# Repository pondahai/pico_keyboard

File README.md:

# Pico 8x8 矩陣鍵盤韌體

這是一個基於 Raspberry Pi Pico (RP2040) 的 8x8 (64鍵) 自訂機械鍵盤韌體專案。它使用 Arduino-Pico 核心，並透過 74HC595 和 74HC165 晶片來擴展 I/O，僅用 3 個 GPIO 引腳就完成了 64 個按鍵的掃描。此外，還額外擴展了 2 個 LED 指示燈。

韌體最終將 Pico 模擬成一個標準的 USB HID 鍵盤，可以被任何現代作業系統即插即用，同時保留了方便的序列埠除錯功能。

**「這句話就是用這個鍵盤輸入的」** —— 專案成功的最好證明！

## ✨ 主要功能

*   **高效 I/O 擴展**：僅用 3 個 Pico GPIO 引腳驅動 8x8 (64鍵) 矩陣和 2 個 LED。
*   **USB HID 鍵盤**：被電腦識別為標準鍵盤，隨插即用。
*   **複合式 USB 裝置**：同時啟用鍵盤功能和序列埠，方便即時除錯。
*   **雙模式系統**:
    *   **正常打字模式**: 作為一個標準鍵盤工作。
    *   **除錯模式**: 透過序列埠輸出按鍵的物理座標 `(row, col)`，極大地方便了 Keymap 的配置與修改。
*   **韌體層級熱鍵**：使用 `右Shift` + `左Ctrl` 組合鍵在兩種模式間自由切換。
*   **LED 狀態指示**:
    *   LED 1: （目前留空，可自訂，例如用於 CapsLock 指示）。
    *   LED 2: 指示當前是否處於除錯模式（亮起 = 除錯模式）。
*   **全鍵無衝 (NKRO)**：底層支援 6-Key Rollover，可透過修改 HID 報告描述符實現全鍵無衝。
*   **高度客製化**: 使用者可以透過修改 `keymap` 陣列輕鬆定義自己的按鍵佈局。
*   **可靠的掃描邏輯**:
    *   採用「二段式脈衝」確保掃描時序穩定。
    *   第一段脈衝給595輸出 第二段脈衝給165載入 
    *   針對 74HC165 的特性自訂 `shiftIn` 邏輯，避免丟失數據。
    *   對硬體掃描數據進行「水平鏡像」，使 `keymap` 的定義符合物理直覺。

## ⚙️ 硬體需求

### 主要元件
*   Raspberry Pi Pico (或任何 RP2040 開發板)
*   1 x 74HC595 (8位元移位暫存器，用於行掃描輸出)
*   1 x 74HC165 (8位元並行輸入移位暫存器，用於列讀取)
*   2 x D型正反器 (或第二顆 74HC595，用於擴展 LED 輸出)
*   8x8 矩陣鍵盤 (64個按鍵和二極體)
*   2 x LED 指示燈
*   下拉電阻 (為 74HC165 的每個輸入引腳配置)

### GPIO 連接

| Pico GPIO | 連接目標                                        | 功能描述                                   |
| :-------- | :---------------------------------------------- | :----------------------------------------- |
| **GP15**  | 74HC595 的 `DS` (Serial Data In)                | 數據輸出 (Pico -> 595)                     |
| **GP14**  | 74HC595 `RCLK` **和** 74HC165 `nPL` (共用)      | 鎖存輸出 (上升緣) / 並行加載輸入 (低電位) |
| **GP26**  | 74HC595 `SHCP` **和** 74HC165 `SHCP` (共用)      | 共用的移位時脈                             |
| **GP27**  | 74HC165 的 `Q7` (Serial Data Out)               | 數據輸入 (165 -> Pico)                     |

### 晶片串接
*   **輸出鏈 (595)**: `Pico GP15` -> `595(IC1) DS` -> `595(IC1) Q7'` -> `DFF(IC2) D` -> ...
*   **時脈與鎖存**：所有晶片的時脈腳和鎖存腳都並聯到對應的 Pico GPIO。

## 🛠️ 軟體設定與編譯

### Arduino IDE 環境
1.  安裝 **Arduino IDE**。
2.  在「開發板管理器」中，安裝 **Earle F. Philhower, III** 的 **Raspberry Pi Pico/RP2040** 核心。
3.  在 **工具 > 開發板** 中選擇 "Raspberry Pi Pico"。
4.  ~**【最重要的一步】** 在 **工具 > USB Stack** 中，選擇 **"Adafruit TinyUSB"**。這會啟用複合式 USB 裝置功能。~
5.  因為gemini一直堅持使用 **"Adafruit TinyUSB"** 但是HID一直無法正常啟用 因此我去找討論區有人提到標準庫可以支援標準的 Keyboard.h 於是USB Stack就切換回Pico SDK 並且使用標準的 Keyboard.h

### 編譯與上傳
1.  用 Arduino IDE 打開 `.ino` 檔案。
2.  連接 Pico 到電腦。
3.  選擇正確的 COM 連接埠。
4.  點擊「上傳」按鈕。

## ⌨️ 使用說明

1.  **初次連接**: 上傳程式碼後，Pico 將被電腦識別為一個複合式裝置（鍵盤 + 序列埠）。
2.  **預設模式**: 韌體預設進入**除錯模式**。此時 **LED 2** 會亮起。
3.  **除錯模式**:
    *   打開 Arduino IDE 的「序列埠監控器」（鮑率設為 115200）。
    *   按下鍵盤上的任意按鍵。
    *   序列埠監控器會顯示一個 8x8 的狀態矩陣，並打印出被按下按鍵的物理座標，例如 `Key Pressed at: (Row: 2, Col: 6)`。
    *   使用這個功能來確認每個按鍵的座標，以便精確修改下方的 `keymap`。
4.  **切換到正常打字模式**:
    *   同時按下 **右 Shift** 和 **左 Ctrl** 鍵。
    *   **LED 2** 將會熄滅。
    *   現在，您的鍵盤可以像一個普通鍵盤一樣，在任何文字編輯器中輸入文字。
5.  **切換回除錯模式**:
    *   再次同時按下 **右 Shift** 和 **左 Ctrl** 鍵即可。

## 📝 Keymap 客製化

要定義您自己的按鍵佈局，您只需要修改原始碼中的 `keymap_hid` 陣列。

```cpp
const uint8_t keymap_hid[8][8] = {
  // COL 0        1         2         3         4         ...
  {HID_KEY_1, HID_KEY_3, HID_KEY_5, ... }, // ROW 0
  {HID_KEY_Q, HID_KEY_E, HID_KEY_T, ... }, // ROW 1
  // ... and so on
};
```
*   陣列的 `[row][col]` 索引與您在**除錯模式**下看到的座標完全對應。
*   陣列中的值是標準的 **USB HID Usage ID**（也稱為 Scancode）。您可以在程式碼頂部的 `#define` 區域找到常用鍵的定義，或查詢相關的 USB HID 文件。
*   這裡應使用除錯模式 透過序列埠監控器觀察硬體按鍵對應的keymap位置 然後去keymap陣列變數中填入正確對應的按鍵。

## 💡 未來可擴展方向

*   實現多層 Keymap (Fn 層)。
*   加入巨集功能。
*   Tap Dance（輕觸/長按不同功能）。
*   RGB LED 燈光效果。
*   OLED 螢幕狀態顯示。

---

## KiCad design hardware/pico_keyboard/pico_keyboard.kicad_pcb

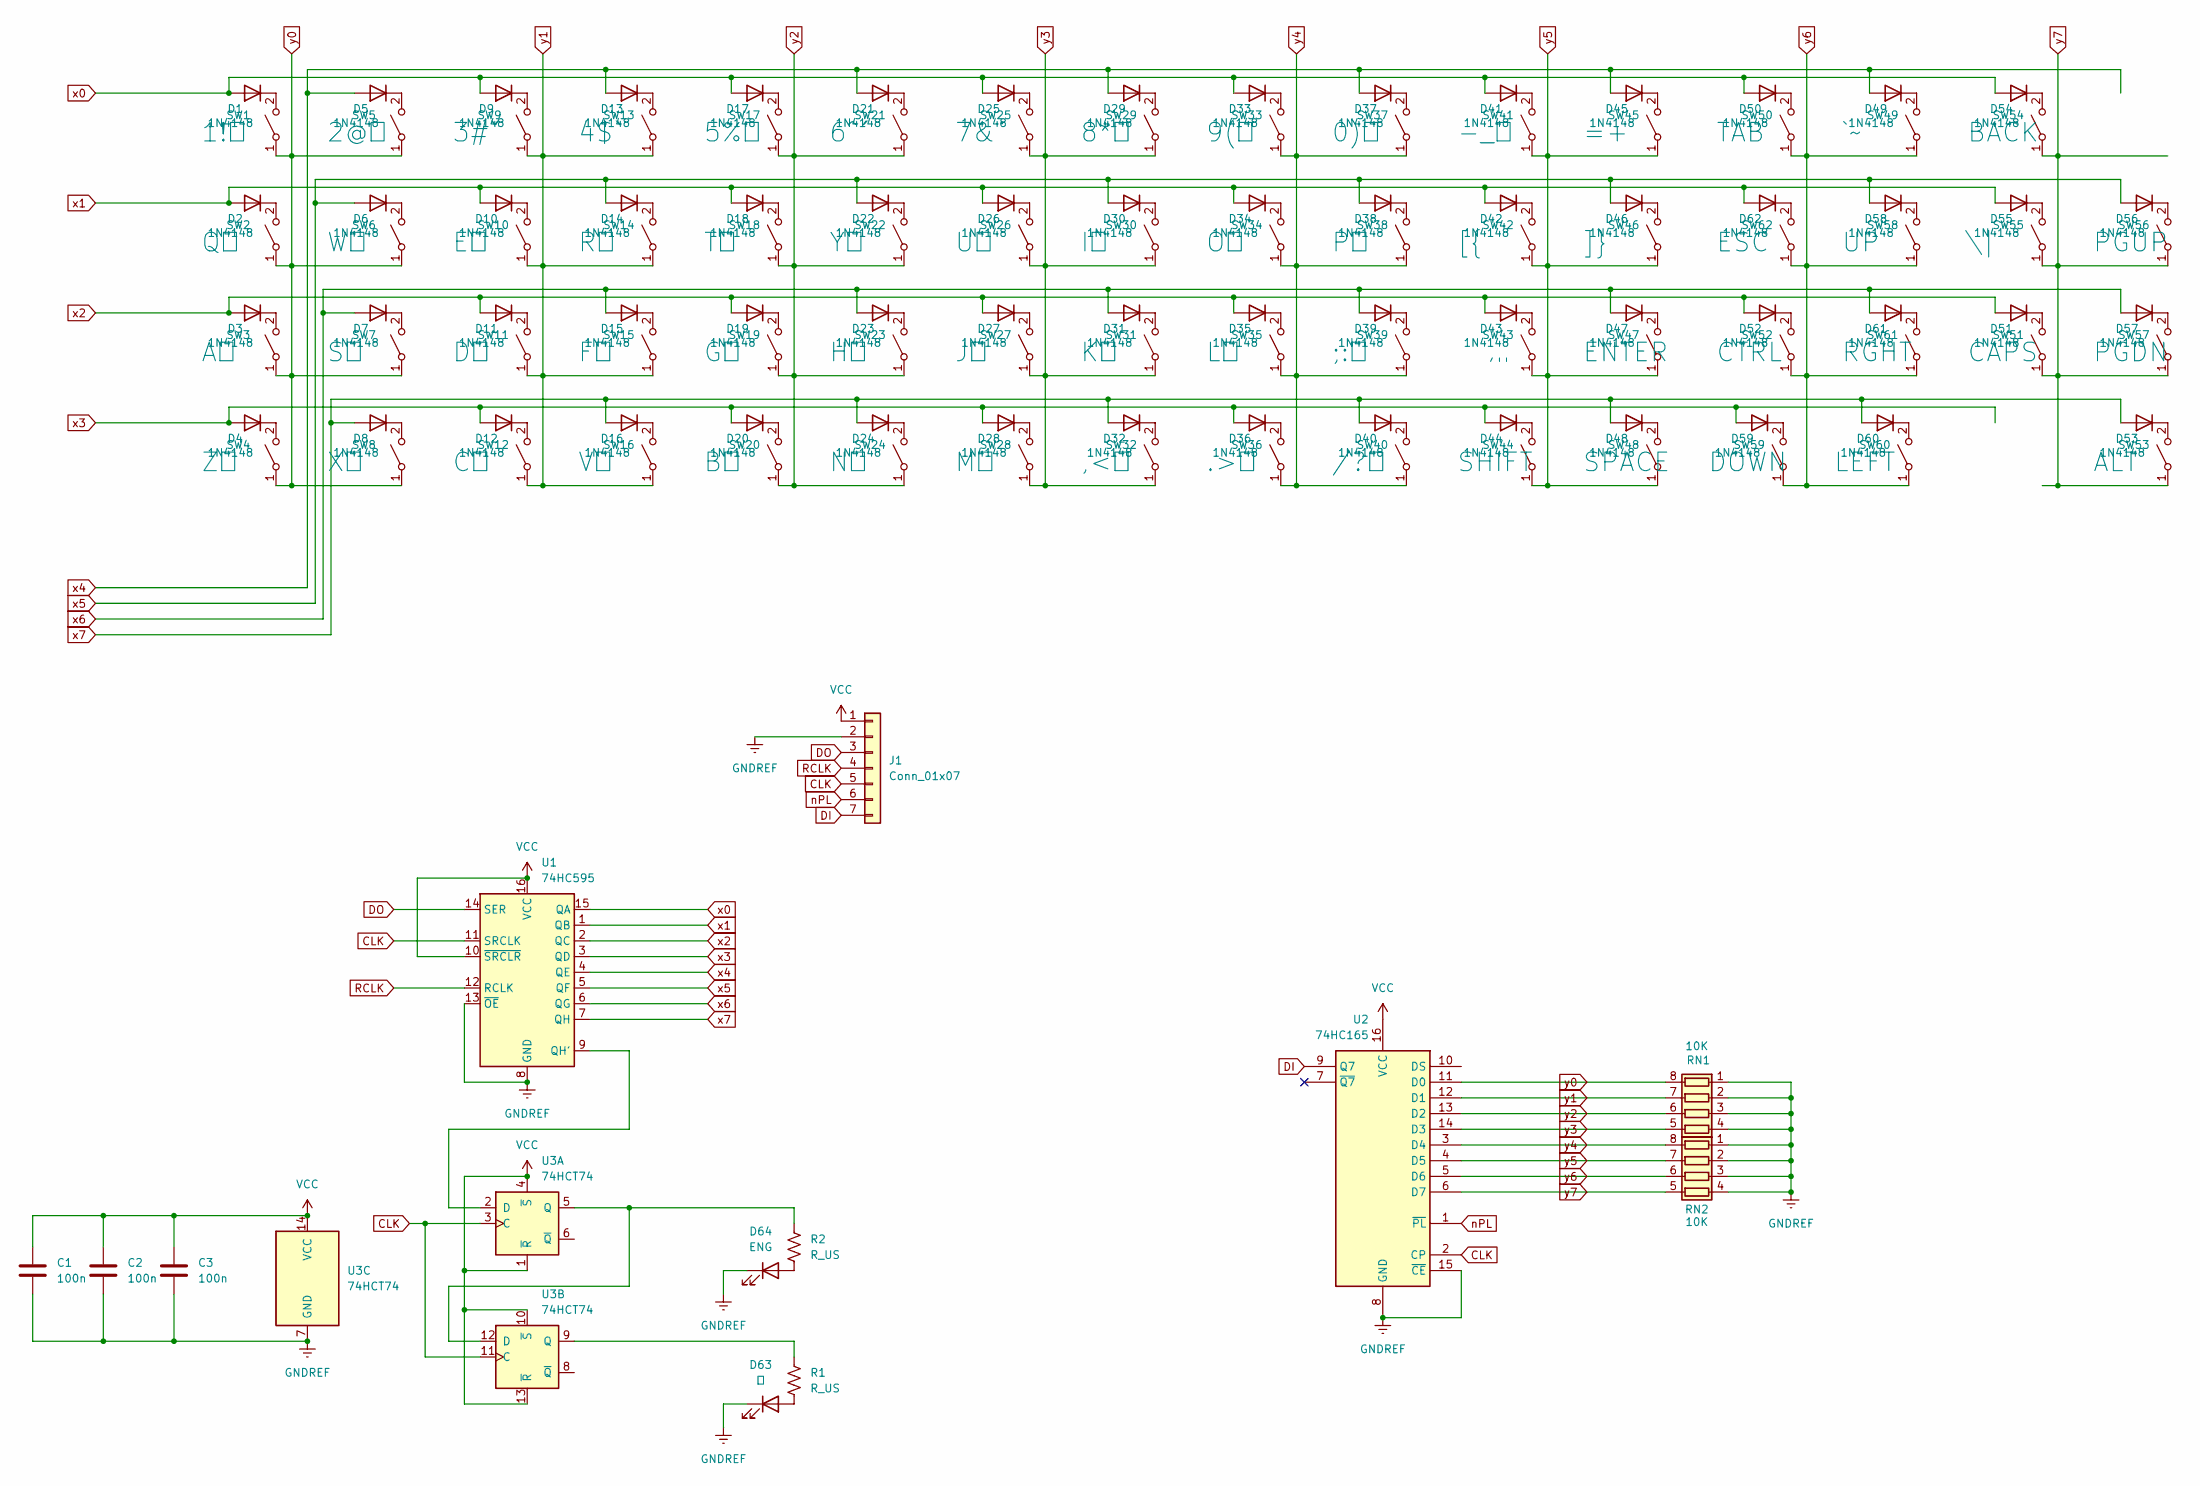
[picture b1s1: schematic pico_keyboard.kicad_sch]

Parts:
C1, C2, C3: 100n; C_0805_2012Metric_Pad1.18x1.45mm_HandSolder
D1, D2, D3, D4, D5, D6, D7, D8, D9, D10, D11, D12, D13, D14, D15, D16, D17, D18, D19, D20, D21, D22, D23, D24, D25, D26, D27, D28, D29, D30, D31, D32, D33, D34, D35, D36, D37, D38, D39, D40, D41, D42, D43, D44, D45, D46, D47, D48, D49, D50, D51, D52, D53, D54, D55, D56, D57, D58, D59, D60, D61, D62: 1N4148; D_DO-35_SOD27_SOD123_P7.62mm_Horizontal
D63: ㄅ; LED_D3.0mm_Clear
D64: ENG; LED_D3.0mm_Clear
J1: Conn_01x07; PinHeader_1x07_P2.54mm_Horizontal
R1, R2: R_US; R_Axial_DIN0204_L3.6mm_D1.6mm_P7.62mm_Horizontal_0805
RN1, RN2: 10K; R_Array_Convex_4x0603
SW1: 1!ㄅ; SW_Push_1P1T_NO_CK_KSC7xxJ
SW2: Qㄆ; SW_Push_1P1T_NO_CK_KSC7xxJ
SW3: Aㄇ; SW_Push_1P1T_NO_CK_KSC7xxJ
SW4: Zㄈ; SW_Push_1P1T_NO_CK_KSC7xxJ
SW5: 2@ㄉ; SW_Push_1P1T_NO_CK_KSC7xxJ
SW6: Wㄊ; SW_Push_1P1T_NO_CK_KSC7xxJ
SW7: Sㄋ; SW_Push_1P1T_NO_CK_KSC7xxJ
SW8: Xㄌ; SW_Push_1P1T_NO_CK_KSC7xxJ
SW9: 3#ˇ; SW_Push_1P1T_NO_CK_KSC7xxJ
SW10: Eㄍ; SW_Push_1P1T_NO_CK_KSC7xxJ
SW11: Dㄎ; SW_Push_1P1T_NO_CK_KSC7xxJ
SW12: Cㄏ; SW_Push_1P1T_NO_CK_KSC7xxJ
SW13: 4$ˋ; SW_Push_1P1T_NO_CK_KSC7xxJ
SW14: Rㄐ; SW_Push_1P1T_NO_CK_KSC7xxJ
SW15: Fㄑ; SW_Push_1P1T_NO_CK_KSC7xxJ
SW16: Vㄒ; SW_Push_1P1T_NO_CK_KSC7xxJ
SW17: 5%ㄓ; SW_Push_1P1T_NO_CK_KSC7xxJ
SW18: Tㄔ; SW_Push_1P1T_NO_CK_KSC7xxJ
SW19: Gㄕ; SW_Push_1P1T_NO_CK_KSC7xxJ
SW20: Bㄖ; SW_Push_1P1T_NO_CK_KSC7xxJ
SW21: 6^ˊ; SW_Push_1P1T_NO_CK_KSC7xxJ
SW22: Yㄗ; SW_Push_1P1T_NO_CK_KSC7xxJ
SW23: Hㄘ; SW_Push_1P1T_NO_CK_KSC7xxJ
SW24: Nㄙ; SW_Push_1P1T_NO_CK_KSC7xxJ
SW25: 7&˙; SW_Push_1P1T_NO_CK_KSC7xxJ
SW26: Uㄧ; SW_Push_1P1T_NO_CK_KSC7xxJ
SW27: Jㄨ; SW_Push_1P1T_NO_CK_KSC7xxJ
SW28: Mㄩ; SW_Push_1P1T_NO_CK_KSC7xxJ
SW29: 8*ㄚ; SW_Push_1P1T_NO_CK_KSC7xxJ
SW30: Iㄛ; SW_Push_1P1T_NO_CK_KSC7xxJ
SW31: Kㄜ; SW_Push_1P1T_NO_CK_KSC7xxJ
SW32: ,<ㄝ; SW_Push_1P1T_NO_CK_KSC7xxJ
SW33: 9(ㄞ; SW_Push_1P1T_NO_CK_KSC7xxJ
SW34: Oㄟ; SW_Push_1P1T_NO_CK_KSC7xxJ
SW35: Lㄠ; SW_Push_1P1T_NO_CK_KSC7xxJ
SW36: .>ㄡ; SW_Push_1P1T_NO_CK_KSC7xxJ
SW37: 0)ㄢ; SW_Push_1P1T_NO_CK_KSC7xxJ
SW38: Pㄣ; SW_Push_1P1T_NO_CK_KSC7xxJ
SW39: ;:ㄤ; SW_Push_1P1T_NO_CK_KSC7xxJ
SW40: /?ㄥ; SW_Push_1P1T_NO_CK_KSC7xxJ
SW41: -_ㄦ; SW_Push_1P1T_NO_CK_KSC7xxJ
SW42: [{; SW_Push_1P1T_NO_CK_KSC7xxJ
SW43: '"; SW_Push_1P1T_NO_CK_KSC7xxJ
SW44: SHIFT; SW_Push_1P1T_NO_CK_KSC7xxJ
SW45: =+; SW_Push_1P1T_NO_CK_KSC7xxJ
SW46: ]}; SW_Push_1P1T_NO_CK_KSC7xxJ
SW47: ENTER; SW_Push_1P1T_NO_CK_KSC7xxJ
SW48: SPACE; SW_Push_1P1T_NO_CK_KSC7xxJ
SW49: `~; SW_Push_1P1T_NO_CK_KSC7xxJ
SW50: TAB; SW_Push_1P1T_NO_CK_KSC7xxJ
SW51: CAPS; SW_Push_1P1T_NO_CK_KSC7xxJ
SW52: CTRL; SW_Push_1P1T_NO_CK_KSC7xxJ
SW53: ALT; SW_Push_1P1T_NO_CK_KSC7xxJ
SW54: BACK; SW_Push_1P1T_NO_CK_KSC7xxJ
SW55: \|; SW_Push_1P1T_NO_CK_KSC7xxJ
SW56: PGUP; SW_Push_1P1T_NO_CK_KSC7xxJ
SW57: PGDN; SW_Push_1P1T_NO_CK_KSC7xxJ
SW58: UP; SW_Push_1P1T_NO_CK_KSC7xxJ
SW59: DOWN; SW_Push_1P1T_NO_CK_KSC7xxJ
SW60: LEFT; SW_Push_1P1T_NO_CK_KSC7xxJ
SW61: RGHT; SW_Push_1P1T_NO_CK_KSC7xxJ
SW62: ESC; SW_Push_1P1T_NO_CK_KSC7xxJ
U1: 74HC595; SOIC-16_3.9x9.9mm_P1.27mm
U2: 74HC165; SOIC-16_3.9x9.9mm_P1.27mm
U3: 74HCT74; SO-14_3.9x8.65mm_P1.27mm

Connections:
CLK: J1.5, U1.11 (SRCLK), U2.2 (CP), U3.3 (C), U3.11 (C)
DI: J1.7, U2.9 (Q7)
DO: J1.3, U1.14 (SER)
GNDREF: C1.2, C2.2, C3.2, D63.1 (K), D64.1 (K), J1.2, RN1.1 (R1.1), RN1.2 (R2.1), RN1.3 (R3.1), RN1.4 (R4.1), RN2.1 (R1.1), RN2.2 (R2.1), RN2.3 (R3.1), RN2.4 (R4.1), U1.8 (GND), U1.13 (~OE), U2.8 (GND), U2.15 (~CE), U3.7 (GND)
unnamed: D1.1 (K), SW1.2 (B)
unnamed: D2.1 (K), SW2.2 (B)
unnamed: D3.1 (K), SW3.2 (B)
unnamed: D4.1 (K), SW4.2 (B)
unnamed: D5.1 (K), SW5.2 (B)
unnamed: D6.1 (K), SW6.2 (B)
unnamed: D7.1 (K), SW7.2 (B)
unnamed: D8.1 (K), SW8.2 (B)
unnamed: D9.1 (K), SW9.2 (B)
unnamed: D10.1 (K), SW10.2 (B)
unnamed: D11.1 (K), SW11.2 (B)
unnamed: D12.1 (K), SW12.2 (B)
unnamed: D13.1 (K), SW13.2 (B)
unnamed: D14.1 (K), SW14.2 (B)
unnamed: D15.1 (K), SW15.2 (B)
unnamed: D16.1 (K), SW16.2 (B)
unnamed: D17.1 (K), SW17.2 (B)
unnamed: D18.1 (K), SW18.2 (B)
unnamed: D19.1 (K), SW19.2 (B)
unnamed: D20.1 (K), SW20.2 (B)
unnamed: D21.1 (K), SW21.2 (B)
unnamed: D22.1 (K), SW22.2 (B)
unnamed: D23.1 (K), SW23.2 (B)
unnamed: D24.1 (K), SW24.2 (B)
unnamed: D25.1 (K), SW25.2 (B)
unnamed: D26.1 (K), SW26.2 (B)
unnamed: D27.1 (K), SW27.2 (B)
unnamed: D28.1 (K), SW28.2 (B)
unnamed: D29.1 (K), SW29.2 (B)
unnamed: D30.1 (K), SW30.2 (B)
unnamed: D31.1 (K), SW31.2 (B)
unnamed: D32.1 (K), SW32.2 (B)
unnamed: D33.1 (K), SW33.2 (B)
unnamed: D34.1 (K), SW34.2 (B)
unnamed: D35.1 (K), SW35.2 (B)
unnamed: D36.1 (K), SW36.2 (B)
unnamed: D37.1 (K), SW37.2 (B)
unnamed: D38.1 (K), SW38.2 (B)
unnamed: D39.1 (K), SW39.2 (B)
unnamed: D40.1 (K), SW40.2 (B)
unnamed: D41.1 (K), SW41.2 (B)
unnamed: D42.1 (K), SW42.2 (B)
unnamed: D43.1 (K), SW43.2 (B)
unnamed: D44.1 (K), SW44.2 (B)
unnamed: D45.1 (K), SW45.2 (B)
unnamed: D46.1 (K), SW46.2 (B)
unnamed: D47.1 (K), SW47.2 (B)
unnamed: D48.1 (K), SW48.2 (B)
unnamed: D49.1 (K), SW49.2 (B)
unnamed: D50.1 (K), SW50.2 (B)
unnamed: D51.1 (K), SW51.2 (B)
unnamed: D52.1 (K), SW52.2 (B)
unnamed: D53.1 (K), SW53.2 (B)
unnamed: D54.1 (K), SW54.2 (B)
unnamed: D55.1 (K), SW55.2 (B)
unnamed: D56.1 (K), SW56.2 (B)
unnamed: D57.1 (K), SW57.2 (B)
unnamed: D58.1 (K), SW58.2 (B)
unnamed: D59.1 (K), SW59.2 (B)
unnamed: D60.1 (K), SW60.2 (B)
unnamed: D61.1 (K), SW61.2 (B)
unnamed: D62.1 (K), SW62.2 (B)
unnamed: D63.2 (A), R1.2
unnamed: D64.2 (A), R2.2
unnamed: U1.9 (QH'), U3.2 (D)
unnamed: R2.1, U3.5 (Q), U3.12 (D)
unnamed: R1.1, U3.9 (Q)
RCLK: J1.4, U1.12 (RCLK)
VCC: C1.1, C2.1, C3.1, J1.1, U1.10 (~SRCLR), U1.16 (VCC), U2.16 (VCC), U3.1 (~R), U3.4 (~S), U3.10 (~S), U3.13 (~R), U3.14 (VCC)
nPL: J1.6, U2.1 (~PL)
x0: D1.2 (A), D9.2 (A), D17.2 (A), D25.2 (A), D33.2 (A), D41.2 (A), D50.2 (A), D54.2 (A), U1.15 (QA)
x1: D2.2 (A), D10.2 (A), D18.2 (A), D26.2 (A), D34.2 (A), D42.2 (A), D55.2 (A), D62.2 (A), U1.1 (QB)
x2: D3.2 (A), D11.2 (A), D19.2 (A), D27.2 (A), D35.2 (A), D43.2 (A), D51.2 (A), D52.2 (A), U1.2 (QC)
x3: D4.2 (A), D12.2 (A), D20.2 (A), D28.2 (A), D36.2 (A), D44.2 (A), D59.2 (A), U1.3 (QD)
x4: D5.2 (A), D13.2 (A), D21.2 (A), D29.2 (A), D37.2 (A), D45.2 (A), D49.2 (A), U1.4 (QE)
x5: D6.2 (A), D14.2 (A), D22.2 (A), D30.2 (A), D38.2 (A), D46.2 (A), D56.2 (A), D58.2 (A), U1.5 (QF)
x6: D7.2 (A), D15.2 (A), D23.2 (A), D31.2 (A), D39.2 (A), D47.2 (A), D57.2 (A), D61.2 (A), U1.6 (QG)
x7: D8.2 (A), D16.2 (A), D24.2 (A), D32.2 (A), D40.2 (A), D48.2 (A), D53.2 (A), D60.2 (A), U1.7 (QH)
y0: RN1.8 (R1.2), SW1.1 (A), SW2.1 (A), SW3.1 (A), SW4.1 (A), SW5.1 (A), SW6.1 (A), SW7.1 (A), SW8.1 (A), U2.11 (D0)
y1: RN1.7 (R2.2), SW9.1 (A), SW10.1 (A), SW11.1 (A), SW12.1 (A), SW13.1 (A), SW14.1 (A), SW15.1 (A), SW16.1 (A), U2.12 (D1)
y2: RN1.6 (R3.2), SW17.1 (A), SW18.1 (A), SW19.1 (A), SW20.1 (A), SW21.1 (A), SW22.1 (A), SW23.1 (A), SW24.1 (A), U2.13 (D2)
y3: RN1.5 (R4.2), SW25.1 (A), SW26.1 (A), SW27.1 (A), SW28.1 (A), SW29.1 (A), SW30.1 (A), SW31.1 (A), SW32.1 (A), U2.14 (D3)
y4: RN2.8 (R1.2), SW33.1 (A), SW34.1 (A), SW35.1 (A), SW36.1 (A), SW37.1 (A), SW38.1 (A), SW39.1 (A), SW40.1 (A), U2.3 (D4)
y5: RN2.7 (R2.2), SW41.1 (A), SW42.1 (A), SW43.1 (A), SW44.1 (A), SW45.1 (A), SW46.1 (A), SW47.1 (A), SW48.1 (A), U2.4 (D5)
y6: RN2.6 (R3.2), SW49.1 (A), SW50.1 (A), SW52.1 (A), SW58.1 (A), SW59.1 (A), SW60.1 (A), SW61.1 (A), SW62.1 (A), U2.5 (D6)
y7: RN2.5 (R4.2), SW51.1 (A), SW53.1 (A), SW54.1 (A), SW55.1 (A), SW56.1 (A), SW57.1 (A), U2.6 (D7)

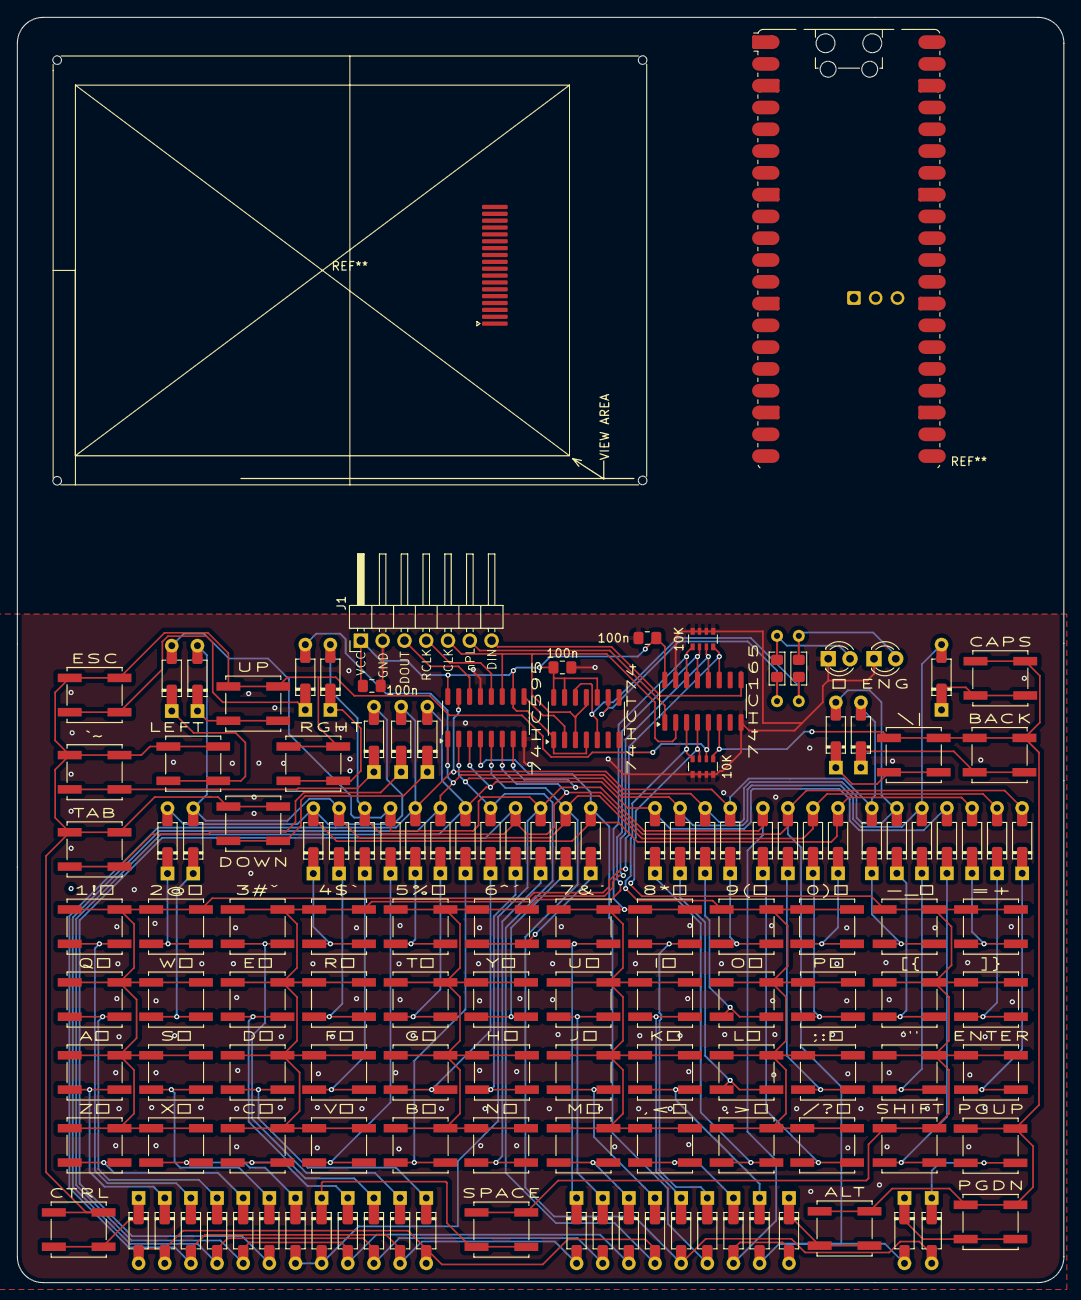
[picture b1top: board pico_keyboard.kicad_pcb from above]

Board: 2 copper layers, 122.0 x 147.5 mm, 137 parts (0 on the bottom side), 90 nets.

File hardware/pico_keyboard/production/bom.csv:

Designator,Footprint,Quantity,Value,LCSC Part #
"C1, C2, C3",0805,3,100n,
"D1, D10, D11, D12, D13, D14, D15, D16, D17, D18, D19, D2, D20, D21, D22, D23, D24, D25, D26, D27, D28, D29, D3, D30, D31, D32, D33, D34, D35, D36, D37, D38, D39, D4, D40, D41, D42, D43, D44, D45, D46, D47, D48, D49, D5, D50, D51, D52, D53, D54, D55, D56, D57, D58, D59, D6, D60, D61, D62, D7, D8, D9",D_DO-35_SOD27_SOD123_P7.62mm_Horizontal,62,1N4148,
D63,LED_D3.0mm_Clear,1,ㄅ,
D64,LED_D3.0mm_Clear,1,ENG,
J1,PinHeader_1x07_P2.54mm_Horizontal,1,Conn_01x07,
"R1, R2",R_Axial_DIN0204_L3.6mm_D1.6mm_P7.62mm_Horizontal_0805,2,R_US,
"RN1, RN2",R_Array_Convex_4x0603,2,10K,
SW1,SW_Push_1P1T_NO_CK_KSC7xxJ,1,1!ㄅ,
SW10,SW_Push_1P1T_NO_CK_KSC7xxJ,1,Eㄍ,
SW11,SW_Push_1P1T_NO_CK_KSC7xxJ,1,Dㄎ,
SW12,SW_Push_1P1T_NO_CK_KSC7xxJ,1,Cㄏ,
SW13,SW_Push_1P1T_NO_CK_KSC7xxJ,1,4$ˋ,
SW14,SW_Push_1P1T_NO_CK_KSC7xxJ,1,Rㄐ,
SW15,SW_Push_1P1T_NO_CK_KSC7xxJ,1,Fㄑ,
SW16,SW_Push_1P1T_NO_CK_KSC7xxJ,1,Vㄒ,
SW17,SW_Push_1P1T_NO_CK_KSC7xxJ,1,5%ㄓ,
SW18,SW_Push_1P1T_NO_CK_KSC7xxJ,1,Tㄔ,
SW19,SW_Push_1P1T_NO_CK_KSC7xxJ,1,Gㄕ,
SW2,SW_Push_1P1T_NO_CK_KSC7xxJ,1,Qㄆ,
SW20,SW_Push_1P1T_NO_CK_KSC7xxJ,1,Bㄖ,
SW21,SW_Push_1P1T_NO_CK_KSC7xxJ,1,6^ˊ,
SW22,SW_Push_1P1T_NO_CK_KSC7xxJ,1,Yㄗ,
SW23,SW_Push_1P1T_NO_CK_KSC7xxJ,1,Hㄘ,
SW24,SW_Push_1P1T_NO_CK_KSC7xxJ,1,Nㄙ,
SW25,SW_Push_1P1T_NO_CK_KSC7xxJ,1,7&˙,
SW26,SW_Push_1P1T_NO_CK_KSC7xxJ,1,Uㄧ,
SW27,SW_Push_1P1T_NO_CK_KSC7xxJ,1,Jㄨ,
SW28,SW_Push_1P1T_NO_CK_KSC7xxJ,1,Mㄩ,
SW29,SW_Push_1P1T_NO_CK_KSC7xxJ,1,8*ㄚ,
SW3,SW_Push_1P1T_NO_CK_KSC7xxJ,1,Aㄇ,
SW30,SW_Push_1P1T_NO_CK_KSC7xxJ,1,Iㄛ,
SW31,SW_Push_1P1T_NO_CK_KSC7xxJ,1,Kㄜ,
SW32,SW_Push_1P1T_NO_CK_KSC7xxJ,1,",<ㄝ",
SW33,SW_Push_1P1T_NO_CK_KSC7xxJ,1,9(ㄞ,
SW34,SW_Push_1P1T_NO_CK_KSC7xxJ,1,Oㄟ,
SW35,SW_Push_1P1T_NO_CK_KSC7xxJ,1,Lㄠ,
SW36,SW_Push_1P1T_NO_CK_KSC7xxJ,1,.>ㄡ,
SW37,SW_Push_1P1T_NO_CK_KSC7xxJ,1,0)ㄢ,
SW38,SW_Push_1P1T_NO_CK_KSC7xxJ,1,Pㄣ,
SW39,SW_Push_1P1T_NO_CK_KSC7xxJ,1,;:ㄤ,
SW4,SW_Push_1P1T_NO_CK_KSC7xxJ,1,Zㄈ,
SW40,SW_Push_1P1T_NO_CK_KSC7xxJ,1,/?ㄥ,
SW41,SW_Push_1P1T_NO_CK_KSC7xxJ,1,-_ㄦ,
SW42,SW_Push_1P1T_NO_CK_KSC7xxJ,1,[{,
SW43,SW_Push_1P1T_NO_CK_KSC7xxJ,1,"'""",
SW44,SW_Push_1P1T_NO_CK_KSC7xxJ,1,SHIFT,
SW45,SW_Push_1P1T_NO_CK_KSC7xxJ,1,=+,
SW46,SW_Push_1P1T_NO_CK_KSC7xxJ,1,]},
SW47,SW_Push_1P1T_NO_CK_KSC7xxJ,1,ENTER,
SW48,SW_Push_1P1T_NO_CK_KSC7xxJ,1,SPACE,
SW49,SW_Push_1P1T_NO_CK_KSC7xxJ,1,`~,
SW5,SW_Push_1P1T_NO_CK_KSC7xxJ,1,2@ㄉ,
SW50,SW_Push_1P1T_NO_CK_KSC7xxJ,1,TAB,
SW51,SW_Push_1P1T_NO_CK_KSC7xxJ,1,CAPS,
SW52,SW_Push_1P1T_NO_CK_KSC7xxJ,1,CTRL,
SW53,SW_Push_1P1T_NO_CK_KSC7xxJ,1,ALT,
SW54,SW_Push_1P1T_NO_CK_KSC7xxJ,1,BACK,
SW55,SW_Push_1P1T_NO_CK_KSC7xxJ,1,\|,
SW56,SW_Push_1P1T_NO_CK_KSC7xxJ,1,PGUP,
SW57,SW_Push_1P1T_NO_CK_KSC7xxJ,1,PGDN,
SW58,SW_Push_1P1T_NO_CK_KSC7xxJ,1,UP,
SW59,SW_Push_1P1T_NO_CK_KSC7xxJ,1,DOWN,
SW6,SW_Push_1P1T_NO_CK_KSC7xxJ,1,Wㄊ,
SW60,SW_Push_1P1T_NO_CK_KSC7xxJ,1,LEFT,
SW61,SW_Push_1P1T_NO_CK_KSC7xxJ,1,RGHT,
SW62,SW_Push_1P1T_NO_CK_KSC7xxJ,1,ESC,
SW7,SW_Push_1P1T_NO_CK_KSC7xxJ,1,Sㄋ,
SW8,SW_Push_1P1T_NO_CK_KSC7xxJ,1,Xㄌ,
SW9,SW_Push_1P1T_NO_CK_KSC7xxJ,1,3#ˇ,
U1,SOIC-16_3.9x9.9mm_P1.27mm,1,74HC595,
U2,SOIC-16_3.9x9.9mm_P1.27mm,1,74HC165,
U3,SO-14_3.9x8.65mm_P1.27mm,1,74HCT74,
